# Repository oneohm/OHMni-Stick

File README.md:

# OHMni-Stick
Ultra Low Force and Displacement Assistive Tech Joystick

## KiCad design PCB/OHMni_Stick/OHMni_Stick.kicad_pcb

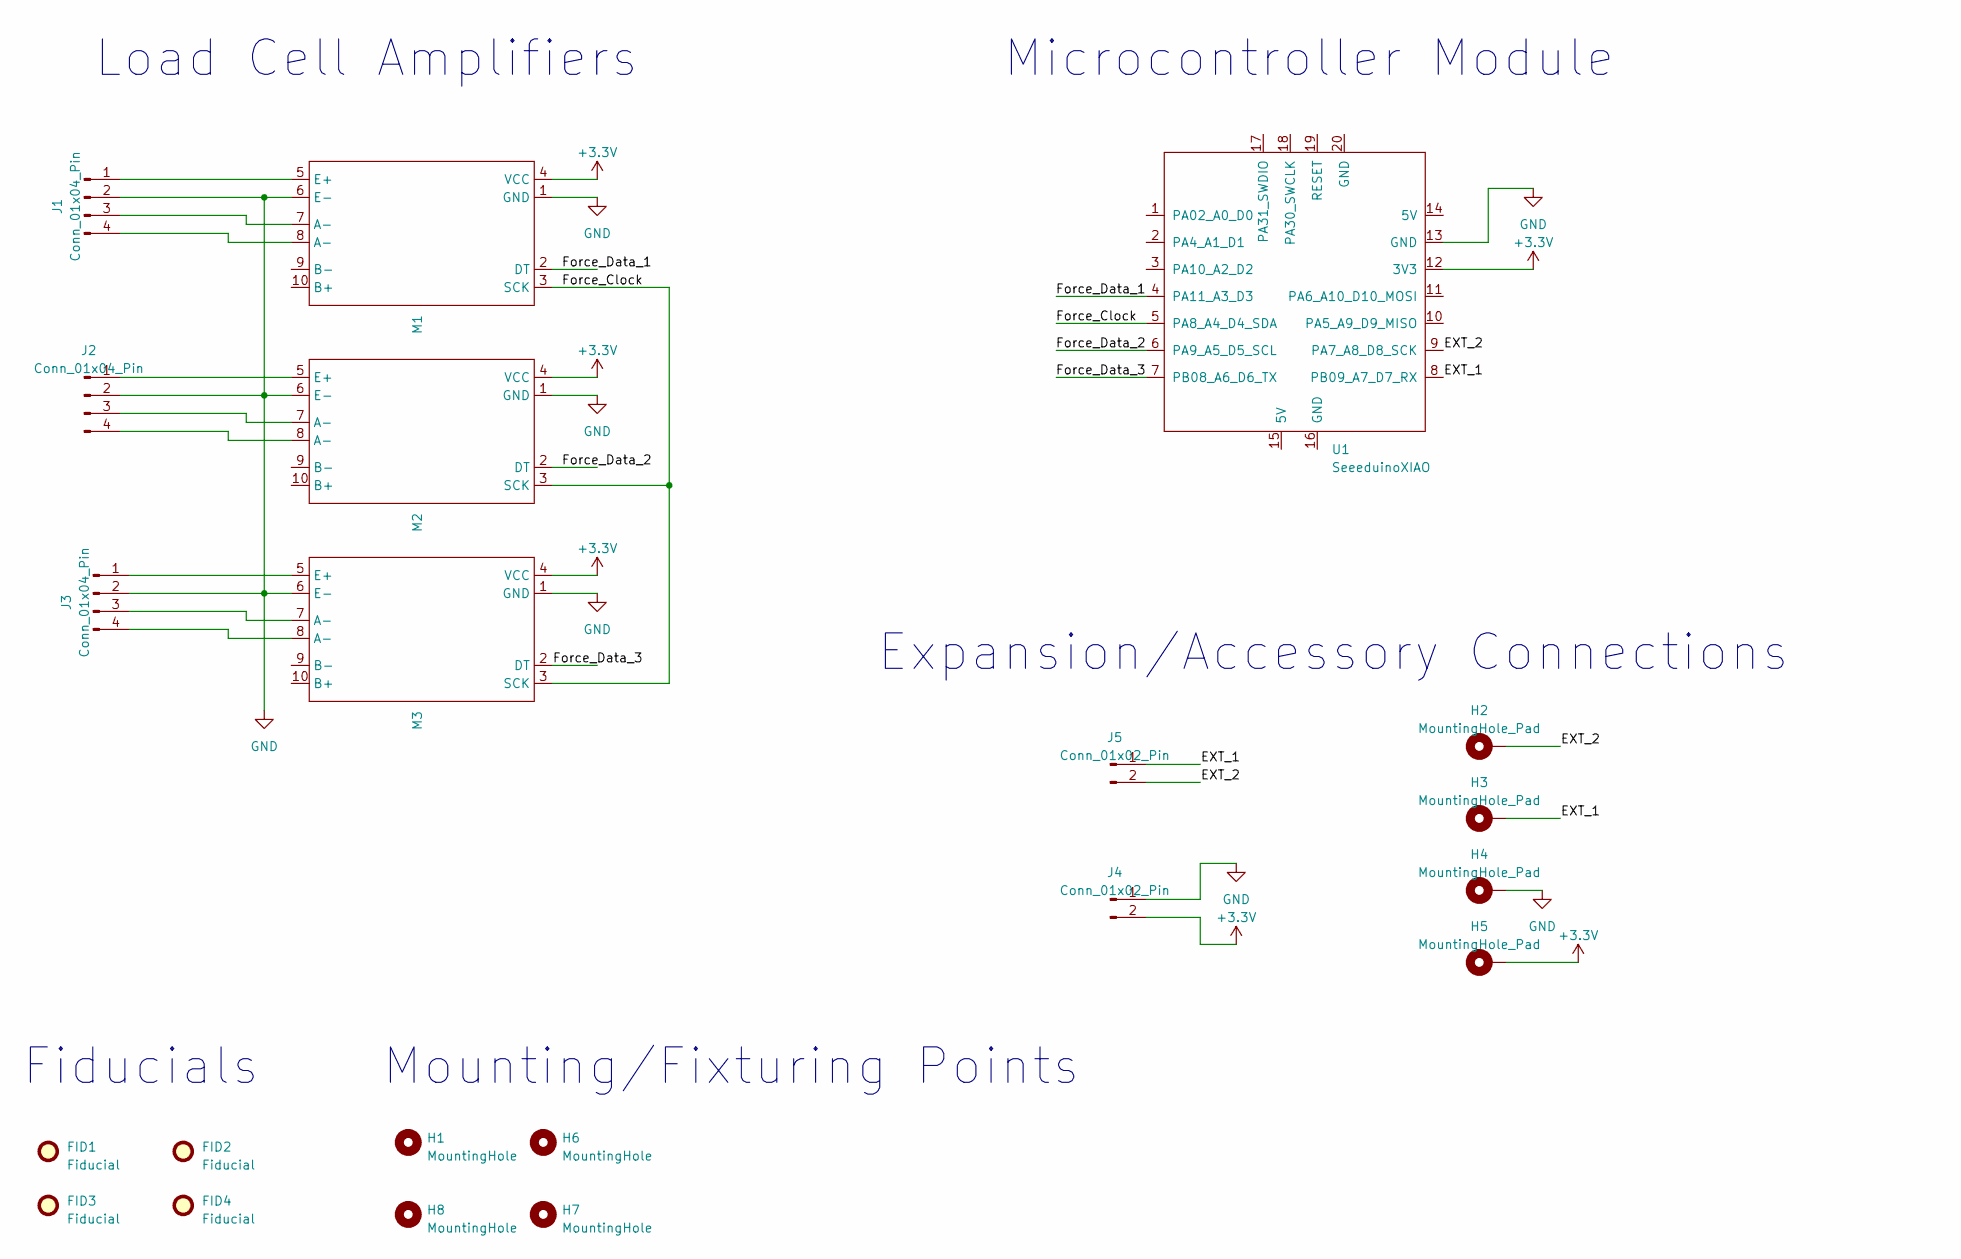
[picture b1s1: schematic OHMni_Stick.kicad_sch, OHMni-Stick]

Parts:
FID1, FID2, FID3, FID4: Fiducial; Fiducial_1mm_Mask3mm
H1, H8: MountingHole; MountingHole_3.2mm_M3_Pad
H2, H3, H4, H5: MountingHole_Pad; MountingHole_3.2mm_M3_Pad
H6, H7: MountingHole; MountingHole_2.9mm_Pad
J1, J2, J3: Conn_01x04_Pin; PinHeader_1x04_P2.54mm_Horizontal_2mm_x_0.8mm_Reversed
J4, J5: Conn_01x02_Pin; PinHeader_1x02_P2.54mm_Horizontal_2mm_x_0.8mm
M1, M2, M3: HX711_Module
U1: SeeeduinoXIAO; Seeeduino XIAO-MOUDLE-Through hole

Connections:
+3.3V: H5.1, J4.2, M1.4 (VCC), M2.4 (VCC), M3.4 (VCC), U1.12 (3V3)
/EXT_1: H3.1, J5.1, U1.8 (PB09_A7_D7_RX)
/EXT_2: H2.1, J5.2, U1.9 (PA7_A8_D8_SCK)
/Force_Clock: M1.3 (SCK), M2.3 (SCK), M3.3 (SCK), U1.5 (PA8_A4_D4_SDA)
/Force_Data_1: M1.2 (DT), U1.4 (PA11_A3_D3)
/Force_Data_2: M2.2 (DT), U1.6 (PA9_A5_D5_SCL)
/Force_Data_3: M3.2 (DT), U1.7 (PB08_A6_D6_TX)
GND: H4.1, J1.2, J2.2, J3.2, J4.1, M1.1 (GND), M1.6 (E-), M2.1 (GND), M2.6 (E-), M3.1 (GND), M3.6 (E-), U1.13 (GND)
unnamed: J1.1, M1.5 (E+)
unnamed: J1.3, M1.7 (A-)
unnamed: J1.4, M1.8 (A-)
unnamed: J2.1, M2.5 (E+)
unnamed: J2.3, M2.7 (A-)
unnamed: J2.4, M2.8 (A-)
unnamed: J3.1, M3.5 (E+)
unnamed: J3.3, M3.7 (A-)
unnamed: J3.4, M3.8 (A-)

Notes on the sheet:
Load Cell Amplifiers
Fiducials
Microcontroller Module
Mounting/Fixturing Points
Expansion/Accessory Connections

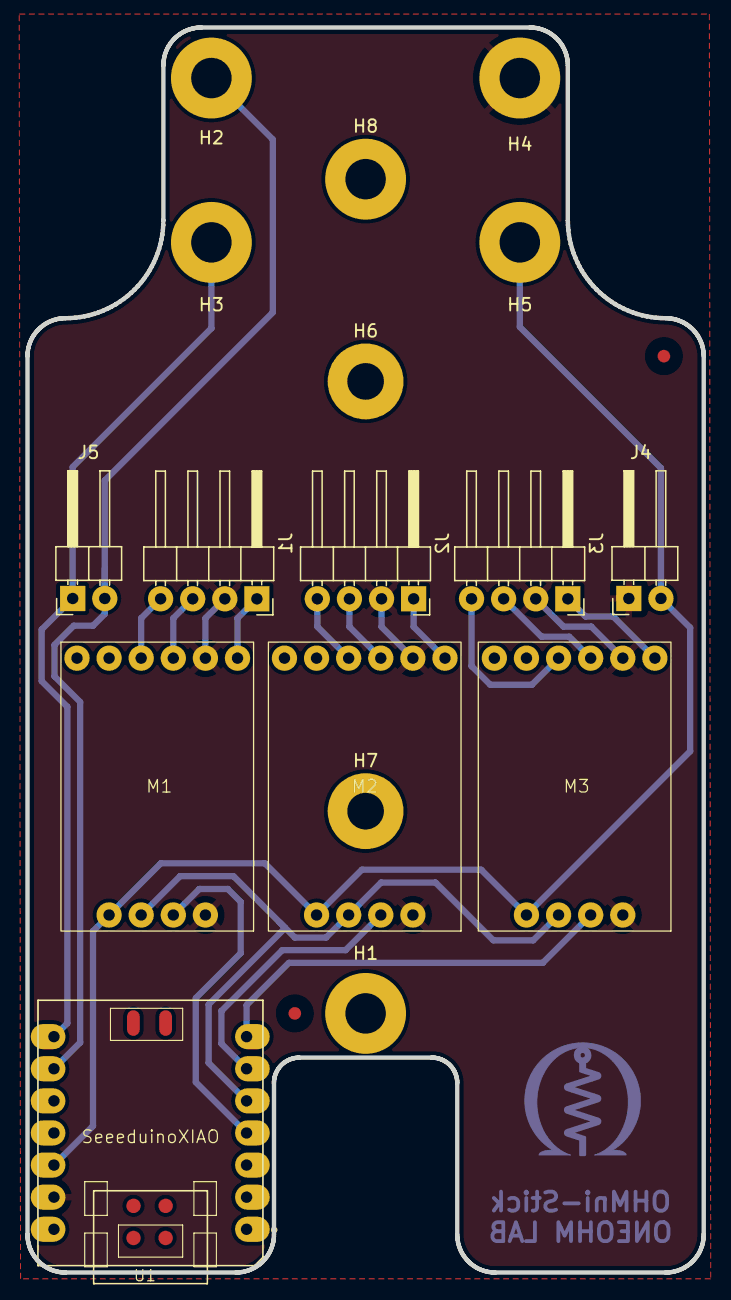
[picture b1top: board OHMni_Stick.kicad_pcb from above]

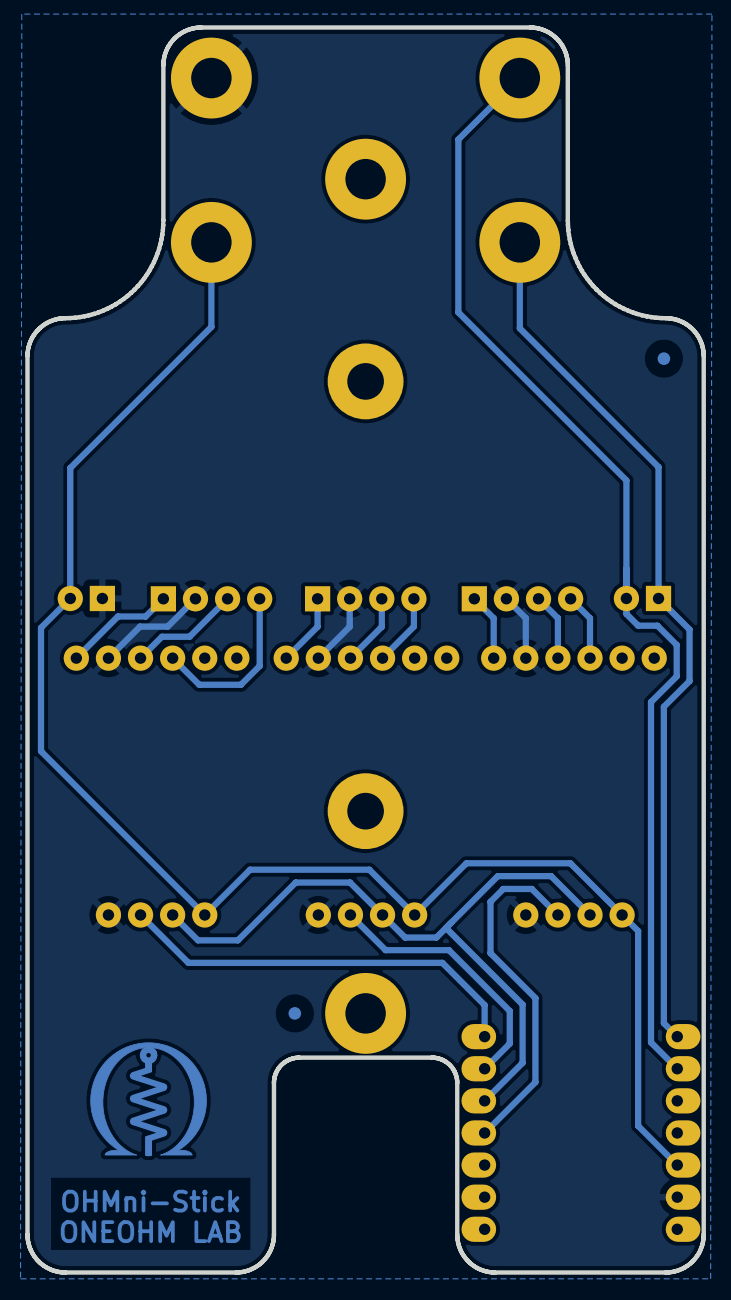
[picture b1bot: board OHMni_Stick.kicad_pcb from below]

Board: 2 copper layers, 53.5 x 98.5 mm, 21 parts (5 on the bottom side), 17 nets.

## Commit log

2023-05-27 Adding firmware to the repository
2023-05-27 Adding Hardware Design
2026-05-22 Add PCB
    Adding KiCad PCB design and gerbers
